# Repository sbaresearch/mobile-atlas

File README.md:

<p align="center">
  
</p>

<p align="center">
  A Scalable Way to Measure Cellular Networks
</p>

MobileAtlas
============

MobileAtlas is a scalable, cost-efficient test framework for cellular networks that takes international roaming measurements to the next level. 
It implements the promising approach to geographically decouple SIM card and modem, which boosts the scalability and flexibility of the measurement platform. It offers versatile capabilities and a controlled environment that makes a good foundation for qualitative measurements. 
Further information can be found on our [website](https://www.mobileatlas.eu/).

### Repository Directories (with README Files)
* root directory (this file): project overview and introduction of the most relevant framework components
* [mobileatlas](/mobileatlas): mobileatlas python modules
* [hardware](/hardware): hardware specification and SIM tunneling technique
* [setup](/setup): setup scripts that are used to install the MobileAtlas framework on a dedicated Raspberry Pi device
* [probe-statuspage](/setup/systemd/probe-statuspage/doc/): documentation of lightweight status page that is running locally on the probes

### Related Repositories
* [mobile-atlas-management](https://github.com/sbaresearch/mobile-atlas-management): management dashboard for admin interactions with deployed probes
* [pySIM](https://github.com/GGegenhuber/pysim): forked version of pySIM that is used by SIM provider and measurement probe
* [masters-thesis](https://github.com/GGegenhuber/masters-thesis): thesis that utilized mobile-atlas to measure traffic classification and zero-rating 
* [wehe-server](https://github.com/phfrenzel/wehe-server): wehe-server that was extended (support for multiple traffic streams, IPv6) and is used for measurements on the MobileAtlas platform
* [wehe-client](https://github.com/phfrenzel/wehe-cmdline): counterpart to the adapted wehe-server; to be used within MobileAtlas the wehe client and pre-recorded traffic recordings are placed within the probe's [measurement implementation](mobileatlas/probe/measurement/payload/res/wehe)

### Publications
* [[GLOBECOM22] Zero-Rating, One Big Mess: Analyzing Differential Pricing Practices of European MNOs](https://www.mobileatlas.eu/papers/22_GLOBECOM_Zero_Rating_One_Big_Mess.pdf)
* [[USENIX Security '23] MobileAtlas: Geographically Decoupled Measurements in Cellular Networks for Security and Privacy Research](https://mobileatlas.eu/papers/23_USENIX_SECURITY_MobileAtlas_Geographically_Decoupled_Measurements_in_Cellular_Networks.pdf)

### Presentations
* [USENIX Security '23] MobileAtlas: Geographically Decoupled Measurements in Cellular Networks for Security and Privacy Research: [Info](https://www.usenix.org/conference/usenixsecurity23/presentation/gegenhuber), [Slides](https://www.usenix.org/system/files/sec23_slides_gegenhuber-gabriel.pdf)
* [DEF CON 31] Cellular Carriers Hate this Trick: Using SIM Tunneling to Travel at Light Speed: [Info](https://info.defcon.org/event/?id=50791), [Recording](https://www.youtube.com/watch?v=MYfeNyZIzBE), [Slides](https://media.defcon.org/DEF%20CON%2031/DEF%20CON%2031%20presentations/Adrian%20atrox%20Dabrowski%20Gabriel%20K.%20Gegenhuber%20-%20Cellular%20carriers%20hate%20this%20trick%20Using%20SIM%20tunneling%20to%20travel%20at%20light%20speed.pdf)
* [GSMA FASG#27] An Open-Source Framework for Rapid Distributed Security Testing and Measurements Based on SIM Tunneling

### Geographical Decoupling of SIM Card and Modem
Physically moving devices and SIM cards between countries to enable measurements in a roaming environment is costly and does not scale well.
Therefore, we introduce an approach to geographically detach the SIM card from the modem by tunneling the SIM card's protocol over the Internet and emulating its signal on the LTE modem.
This allows us to test roaming effects on a large number of operators without physically moving any hardware between different countries.
More specific details regarding the technical implementation of the SIM tunneling technique can be found in the [README file](/hardware#sim-tunneling) of the hardware directory.

### Framework Architecture
The framework can be structured into three main components: SIM providers that allow sharing SIM card access, measurement probes that act as a local breakout to the cellular network, and a management server that connects the prior two components and acts as command and control unit for the measurement probes.

#### SIM Provider
The SIM provider is used to remotely make one or more SIM cards available to the measurement platform.
For communication between the computer and the SIM card, we rely on a [modified version of pySim](https://github.com/GGegenhuber/pysim).
The python file that implements the SIM provider is [sim.py](/sim.py) and uses the [simprovider](/mobileatlas/simprovider) python module (virtualenv required).
More specific details regarding the hardware requirements can be found in the [README file](/hardware#sim-provider) of the hardware directory.

#### Measurement Probe
MobileAtlas probes are responsible for measurement execution.
Each probe consists of a single-board computer with at least an Internet uplink, USB host support, and a GPIO interface.
The python file that is used for test execution on a measurement probe is [probe.py](/probe.py) and uses the [probe](/mobileatlas/probe) python module (virtualenv required).
A detailed breakdown of all used hardware components can be found in the in the [README file](/hardware#measurement-probe) of the hardware directory.

##### Measurement Probe Deployment During Current Fieldtest
MobileAtlas is currently deployed in eight European countries: Austria, Belgium, Croatia, Finland, Germany, Romania, Slovakia, and Slovenia.
Although our focus lies on countries within the EU we also have measurement probes in two American countries: Canada and USA.

We are looking for early adopters, who share interest in the topic and like to contribute to the success of MobileAtlas.
Right now, we need people (or organizations, universities, research institutes, etc.) that host measurement probes. 
Further information can be found on our [website](https://www.mobileatlas.eu/).

Acknowledgments
---------------------------------------
MobileAtlas was developed at [SBA Research](https://www.sba-research.org/) and [University of Vienna](https://sec.cs.univie.ac.at/) by 
[Gabriel K. Gegenhuber](https://www.sba-research.org/team/gabriel-k-gegenhuber/),
[Wilfried Mayer](https://www.sba-research.org/team/wilfried-mayer/),
[Adrian Dabrowski](https://www.sba-research.org/team/adrian-dabrowski/), and
[Philipp Frenzel](https://www.sba-research.org/team/philipp-frenzel/).

Additionally, thanks go to [Markus Maier](https://www.sba-research.org/team/markus-maier/) for his occasional advice and his help designing the [SIM PCB](/hardware/sim-adapter).

Furthermore, we want to thank all hosters of measurement probes who made this work possible at all.

### Funding
This project was funded through the [NGI0 Entrust](https://nlnet.nl/entrust) Fund, a fund established by [NLnet](https://nlnet.nl/) with financial support from the European Commission's [Next Generation Internet](https://ngi.eu/), under the aegis of DG Communications Networks, Content and Technology under grant agreement No 101069594.

This project was funded through the [NGI0 PET](https://nlnet.nl/PET) Fund, a fund established by [NLnet](https://nlnet.nl/) with financial support from the European Commission's [Next Generation Internet](https://ngi.eu/) programme, under the aegis of DG Communications Networks, Content and Technology under grant agreement No 825310.

This research was also funded by the Austrian Science Fund (FWF): P30637-N31.

### Image credits

[Blank map of Europe](https://commons.wikimedia.org/wiki/File:Blank_map_of_Europe_cropped.svg), licensed under [Creative Commons Attribution-ShareAlike 3.0 Unported](https://creativecommons.org/licenses/by-sa/3.0/deed.en)

License
---------------------------------------

MobileAtlas is licensed under GPLv3

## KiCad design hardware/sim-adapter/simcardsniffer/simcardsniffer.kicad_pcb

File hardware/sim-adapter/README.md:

# Mobile Atlas SIM Card Adapter

The PCB is designed to be inserted into the (micro) SIM card socket of the [Sixfab Raspberry Pi LTE Base HAT](https://sixfab.com/product/raspberry-pi-base-hat-3g-4g-lte-minipcie-cards/).  
It attaches to the RST and IO pin of the SIM card that are required for APDU tunneling.  
To make the IO pin compatible with the Raspberry's UART we add a Schottky diode between RX and TX.  

PCB Preview
-----------

Prototype (selfmade CNC)
-----------

Prototype (via JLCPCB)
-----------

Credits
-----------
Thanks to [Markus Maier](https://www.sba-research.org/team/markus-maier/) for designing the PCB.

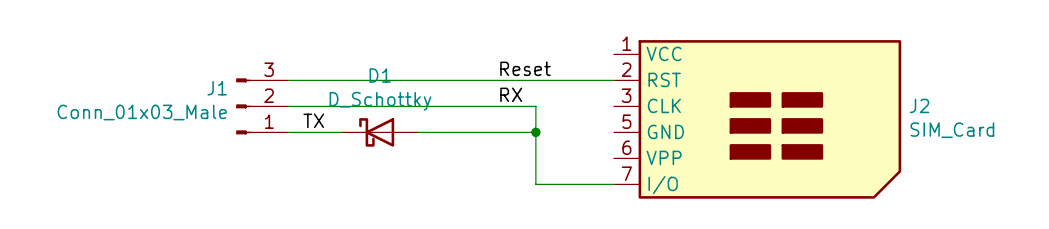
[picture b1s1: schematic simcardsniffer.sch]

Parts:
D1: D_Schottky; D_SOD-123
J1: Conn_01x03_Male; PinHeader_1x03_P2.54mm_Vertical
J2: SIM_Card; microSIM_sniffer

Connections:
/RX: D1.2 (A), J1.2, J2.7 (I/O)
/Reset: J1.3, J2.2 (RST)
/TX: D1.1 (K), J1.1

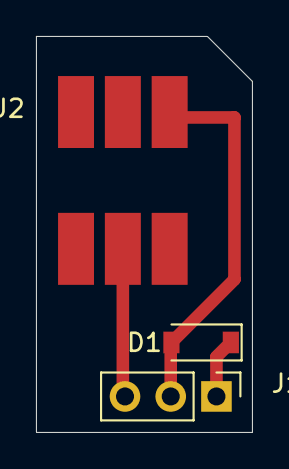
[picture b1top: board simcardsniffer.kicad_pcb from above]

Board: 2 copper layers, 12.0 x 22.0 mm, 3 parts (0 on the bottom side), 3 nets.

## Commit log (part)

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2021-11-03 adapt sim provider to most recent pysim changes
2021-11-03 fix access permissions of executable files
2021-11-04 Update README: adapt sim tunneling summary
2021-11-04 remove unused imports
2021-12-07 pin httpx version to make it work with quic implemenation
2021-12-07 add ansible patch for git repo redesign
2022-02-09 refactor network tests
2022-02-10 refactor network payloads and tests; add dns test
2022-02-23 use primary dns only during dns test
2022-02-23 use payload size instead of consumed size when waiting for bill
2022-02-23 revert changes
2022-02-26 improve dns test implementation
2022-02-27 refactor network payloads and tests; add dns test (#1)
2022-02-27 add wehe test implementation
2022-03-11 update romanian credit checker
2022-03-12 add first draft for hr telemach credit checker
2022-03-12 fix hr telemach creditchecker
2022-03-12 fix ro telekom creditchecker
2022-03-13 add drafts of sk creditchecker
2022-03-13 toggle ro telekom to use used bytes instead of remaining bytes because it is finally correctly displayed in the backend with the new tariff 'R12'
2022-03-13 edit telekom romania creditchecker once again...
2022-03-14 appbased creditchecker sk o2 working
2022-03-14 fix sk credit checker
2022-03-16 rewrite sk orange credit checker
2022-03-16 fix stupid url copy paste error
2022-03-16 remove print from creditchecker
2022-03-16 fix sign at sk orange creditchecker
2022-03-17 improve support for various modems
2022-03-18 improve support of other modem types
2022-03-18 add si a1 creditchecker
2022-03-19 minor fixes in creditchecker
2022-03-19 orange romania again....
2022-03-19 prepare ro_orange for domestic usage
2022-03-19 add initial draft for a1 slovenia
2022-03-20 fix si a1 credit checker
2022-03-20 add slovenia telekom creditchecker
2022-03-20 asdf
2022-03-20 fix si telekom creditchecker
2022-03-20 add si 4ka creditchecker
2022-03-20 fix sk 4ka credit
2022-03-20 prepare sk 4ka for roaming usage
2022-03-20 add pdp_type to network props
2022-03-22 minmor improvements;add sim provider benchmark
2022-03-22 add ip check at ctrl traffic
2022-03-23 update credit checker hr a1
2022-03-23 fix ussd sending
2022-03-23 fix stupid typo...
2022-03-24 increase timeout since website sometimes needs long to respond...
2022-03-28 update wehe jar file
2022-04-04 minor fixes after refactoring
2022-04-21 remove pdp clearance to cleanup --> get ds ip working with qmi
2022-04-22 overwork sim provider to work with dynamically plugged sim cards
2022-04-22 remove temporary test configs
2022-05-04 update wehe files
2022-05-04 get measurements working wwith pv6 via qmi
2022-05-06 fix ipv6 functionality within web payloads
2022-05-08 fix bug in zeroweb test
2022-05-17 adapt sni test to work within ipv6 environments
2022-05-17 wait for udev device instead using a fixed sleep at the start of a measurement
2022-05-17 add timer at modem reset
2022-05-17 fix host ordering (ipv4/v6) at resolv uitls
2022-08-02 improve call functionality; add ringbacktone tests
2022-08-02 add bluetooth (rsap) link to sim provider
2022-08-02 integrate delay-wg-startup.yml into main setup script
2022-08-02 integrate prepare-ns-portforward.yml into main setup script
2022-08-02 integrate uhubctrl_pppd.yml into main setup script
2022-08-02 disable networkmanager to prevent clashes with dhcpcd
2022-08-02 update git repositories in setup script
2022-08-05 move patch of modem interface to enter_ns script
2022-08-05 fix issues after refactoring enter_ns wrapper
2022-08-05 fix pexpect timout bug...
2022-08-05 disable tty login; add some packages to setup script
2022-09-28 add wehe pcap definitions
2022-10-25 add hardware candidate list for 5g probe version
2022-10-28 first draft of local status page
2022-10-29 minor fixes to get status page running
2022-10-29 add simple test logging to probe
2022-10-29 probe statuspage running
2022-10-30 update style.css to match with public website
2022-10-30 revert changes in wireguard-register script since we want it to be standalone (more failsafe)
2022-10-30 add ansible script to install statuspage
2022-10-30 add status page doc
2022-10-30 add status page and wehe stuff to readme
2022-10-30 fix link in readme
2022-10-30 rearrange hardware readme: move 5g candidate list up
2022-10-30 fix typo
2023-01-20 Return SIM identifier from wait_for_connection
2023-01-25 fix imports
2023-01-25 Encode IMSI/ICCID as strings
2023-01-25 Fix merge conflict
2023-02-08 Create package using setuptools
2023-02-08 Fix pyproject.toml files
2023-02-08 Update requirements
2023-02-15 Initial database schema and rest api
2023-02-28 Add Alembic configuration
2023-03-06 Add REST registration API
2023-03-06 Remove API token from AuthRequest message
2023-03-06 Add deregistration endpoint
2023-03-07 bump pysim version to fix apdu handling (at deviating return lengths)
2023-03-07 Remove token parameter from clients
2023-03-07 update acknowledgements in README
2023-03-07 Use API token in dependency
2023-03-07 Use main branch in dependency
2023-03-08 bump version/commit of pysim dependency in requests.txt
2023-03-08 add usenix paper title to readme
2023-03-08 adjust acknowledgement section
2023-03-10 adapt funding acks
2023-03-14 Allow reregistration of SIMs
    Also implements a single registration endpoint
    used by both Probe- and Provider-Clients
2023-03-14 Add requests dependency
2023-03-20 Change clients package to support python 3.7
2023-03-21 Apply linter suggestions
2023-03-28 adapt config.txt to prepare gpio pins for 5g modem adapter
2023-03-28 adapt sourcecode to work with m2 adapter and 5g modem
2023-03-28 fix modem device id format
2023-03-28 fix default modem adapter state
2023-05-02 add reference to paper pdf
2023-05-02 Refactor auth module
    Move db logic from routes to auth module and add timezone
    (un)marshalling.
2023-05-02 Wrap APDU-Tunnel in TLS
2023-05-08 Set isolation level to SERIALIZABLE
2023-05-14 Implement TLS support for clients
2023-05-14 Fix a bug with error handling
2023-05-14 Move errors to their own module
2023-05-16 Add LICENSE and README
2023-05-16 Update dependencies
2023-05-16 Use the new SIM tunnel server
2023-07-04 adding SPDX comment headers about licensing and copyright information
2023-07-14 Update licensing and copyright information
    Remove SPDX headers from `__init__.py` files
    Add CC-BY-SA license to images
    Change license of `requirements.txt` files to CC0
2023-07-18 add wireguard token auth mechanism
2023-08-10 Add Raspberry Pi OS image patching script
2023-08-10 Implement encrypted direct tunnel
    (Re-)adds the ability for probes to directly connect to SIM providers.
2023-08-10 Remove dependencies on private git repos
2023-08-10 Freeze dependencies in requirements.txt
2023-11-10 Add presentations to README.md
2024-02-19 Temporary commit
2024-02-19 Move management server into its own project dir
2024-02-20 Implement timeout logic
2024-02-20 server: start migration to fastapi/postgresql
2024-02-20 Add no_wait flag to con. reqs and finish migration
2024-02-20 Switch to "src" project layout
2024-02-20 Migrate sqlalchemy models to postgresql
2024-02-20 Fix __eq__ bug in Imsi and Iccid types
2024-02-20 Add Makefile and nix flakes
2024-02-20 clients: Add documentation and format code
2024-02-20 Format code
2024-02-20 Update db session usage in auth modules
2024-02-20 Update alembic configuration
2024-02-20 types: Update formatting
2024-02-20 server: Add new configuration class
2024-02-20 server: Add pyproject.toml file
2024-02-20 server: Update formatting
2024-02-27 update pip dependencies (fix pybluez error)
2024-03-04 Started to implement pluggable auth
2024-04-02 Update SIM tunnel
2024-04-02 Update Management Server
2024-04-02 Update documentation
2024-04-03 Update client scripts to use updated SIM tunnel
2024-04-03 Update Nix flakes and add lock files
2024-05-02 add qmi proxy for mbn functionalities
2024-05-02 add sample test_config.json
2024-05-02 Update Makefile and freeze python dependencies
2024-05-02 Consolidate individual Nix flakes into one
2024-05-02 Update READMEs
2024-05-02 Remove unused dev deps from mangement server
2024-05-02 Add .mailmap
2024-05-03 Update READMEs and add missing gunicorn dependency
2024-07-10 Use compatible version specifier for library deps
2024-07-12 Add TLS cert creation Makefile
2024-07-29 Bugfix: _QUEUES dict was mutated during iteration
2024-07-29 Retry initial DB connection on failure
2024-07-29 Implement password hashing for config file
2024-07-29 Fix ISO duration parsing for config files
2024-07-29 Move wg interface management to external service
2024-07-29 Handle cmdline args in tunnel server configuration
2024-07-29 Rename client base class
2024-07-29 Split tunnel container image and update reqs
2024-09-19 Add Basic Auth to management server's tunnel interface
2024-09-19 Change TLS verify mode to CERT_REQUIRED
2024-09-19 Vendor jquery and fonts
2024-09-19 Remove wireguard peers on token revocation
2024-09-19 Fix formatting
2024-09-19 Don't change candidate column on token activation
2024-09-19 Add remove endpoint to wg-daemon
2024-09-19 Fix pyright errors
2024-09-19 Support unix domain sockets for wireguard daemon
2024-09-19 Add container creating flake apps
2024-09-19 Remove unused dependency
2024-09-19 Use x-real-ip header to determine ip when proxied
2024-09-19 Add support for unix sockets to auth handler
2024-09-19 Implement daemon handling the wg interface
2024-09-19 Change log level of periodic messages to debug
2024-09-19 Disable FastAPI documentation by default
2024-09-19 Remove 'behind_proxy' config option
2024-09-19 Remove 'update-python-requirements' git dependency
2024-09-25 Update probe image patching script
2024-09-25 Update 'pi-setup' ansible playbook for new probes
2024-09-25 Update python dependency: requests
2024-09-25 Accept all 2XX responses in probe service scripts
2024-09-25 Replace broken link
2025-06-08 add sdr feasibility documentation
2025-06-09 complete nuc specification
